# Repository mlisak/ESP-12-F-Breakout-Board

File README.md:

## ESP-12-F Breakout Board
This is a simple plug&play breakout board for ESP-12-F cheap Wi-Fi board (22 pins with SPI, 4 MB flash). The design is small, two-sided, and fits nicely on a breadboard. All 22 pins are available on pin headers. The board includes micro USB port, 3.3 V stabilizer, flash/reset buttons and USB-to-serial converter (CH340G/CH340T). Works well with NodeMCU firmware.

Schematic is based on [this design](https://github.com/markbeee/ESP8266_Breakout_Board).

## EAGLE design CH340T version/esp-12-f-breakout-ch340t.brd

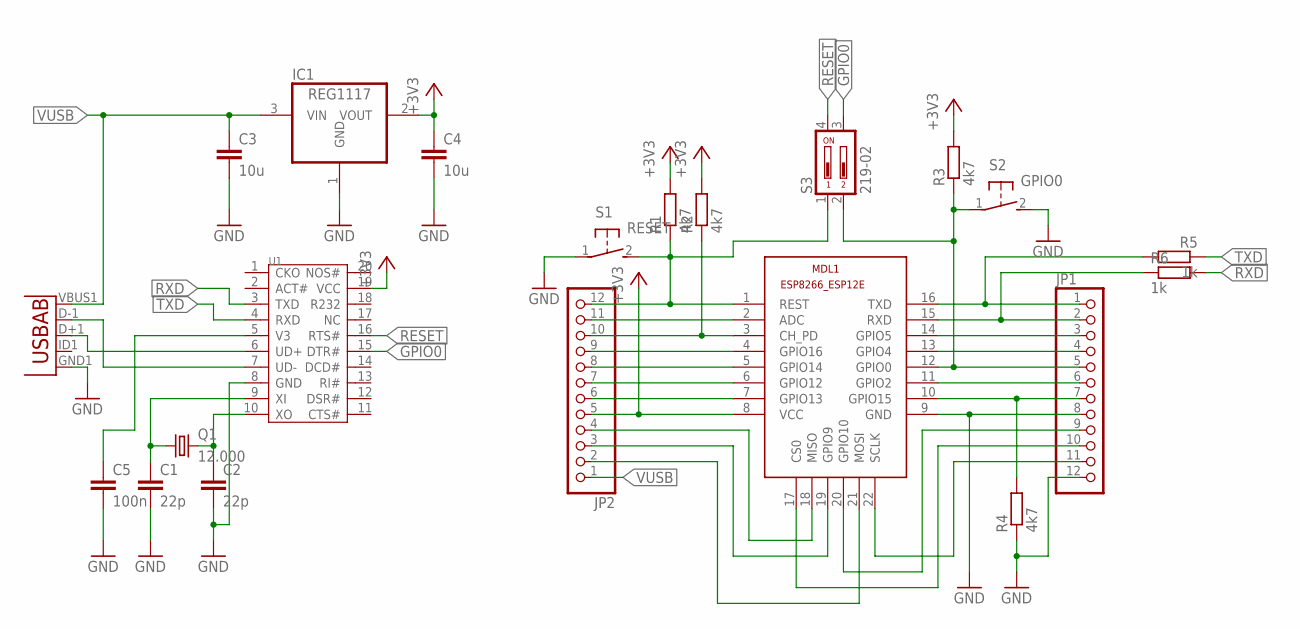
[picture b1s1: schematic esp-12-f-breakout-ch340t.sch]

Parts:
C1, C2: 22p; C0805
C3, C4: 10u; C0805
C5: 100n; C0805
IC1: REG1117; SOT223
JP1, JP2: PINHD-1X12; 1X12
MDL1: ESP8266-12EESP8266-ESP12E; ESP8266-ESP12E
Q1: 12.000; HC49UP
R1, R2, R3, R4: 4k7; M0805
R5, R6: 1k; M0805
S1: RESET; DTSM-3
S2: GPIO0; DTSM-3
S3: 219-02; CTS-219-02
U1: CH340T; SSOP20
U2: USB""; USB-MICRO-SMD

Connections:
+3V3: C4.1, IC1.2 (VOUT), JP2.5, MDL1.8 (VCC), R1.2, R2.2, R3.2, U1.19 (VCC)
GND: C1.2, C2.2, C3.2, C4.2, C5.2, IC1.1 (GND), JP1.8, JP1.12, MDL1.9 (GND), R4.1, S1.1, S2.2, U1.8 (GND), U2.GND1 (GND)
GPIO0: S3.3, U1.15 (DTR#)
unnamed: JP2.12, MDL1.1 (REST), R1.1, S1.2, S3.1
unnamed: JP2.11, MDL1.2 (ADC)
unnamed: JP2.10, MDL1.3 (CH_PD), R2.1
unnamed: JP2.9, MDL1.4 (GPIO16)
unnamed: JP2.8, MDL1.5 (GPIO14)
unnamed: JP2.7, MDL1.6 (GPIO12)
unnamed: JP2.6, MDL1.7 (GPIO13)
unnamed: JP2.4, MDL1.18 (MISO)
unnamed: JP2.3, MDL1.19 (GPIO9)
unnamed: JP1.9, MDL1.20 (GPIO10)
unnamed: JP1.10, MDL1.17 (CS0)
unnamed: JP1.11, MDL1.22 (SCLK)
unnamed: JP2.2, MDL1.21 (MOSI)
unnamed: JP1.7, MDL1.10 (GPIO15), R4.2
unnamed: JP1.6, MDL1.11 (GPIO2)
unnamed: JP1.5, MDL1.12 (GPIO0), R3.1, S2.1, S3.2
unnamed: JP1.4, MDL1.13 (GPIO4)
unnamed: JP1.3, MDL1.14 (GPIO5)
unnamed: JP1.2, MDL1.15 (RXD), R6.1
unnamed: JP1.1, MDL1.16 (TXD), R5.2
unnamed: C1.1, Q1.1, U1.9 (XI)
unnamed: C2.1, Q1.2, U1.10 (XO)
unnamed: U1.7 (UD-), U2.D-1 (D-)
unnamed: U1.6 (UD+), U2.D+1 (D+)
RESET: S3.4, U1.16 (RTS#)
RXD: R6.2, U1.3 (TXD)
TXD: R5.1, U1.4 (RXD)
V3: C5.1, U1.5 (V3)
VUSB: C3.1, IC1.3 (VIN), JP2.1, U2.VBUS1 (VBUS)

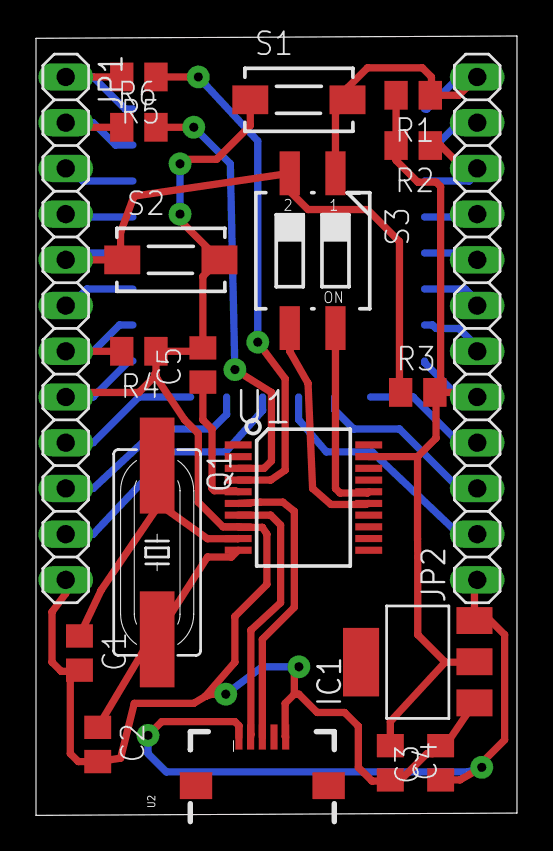
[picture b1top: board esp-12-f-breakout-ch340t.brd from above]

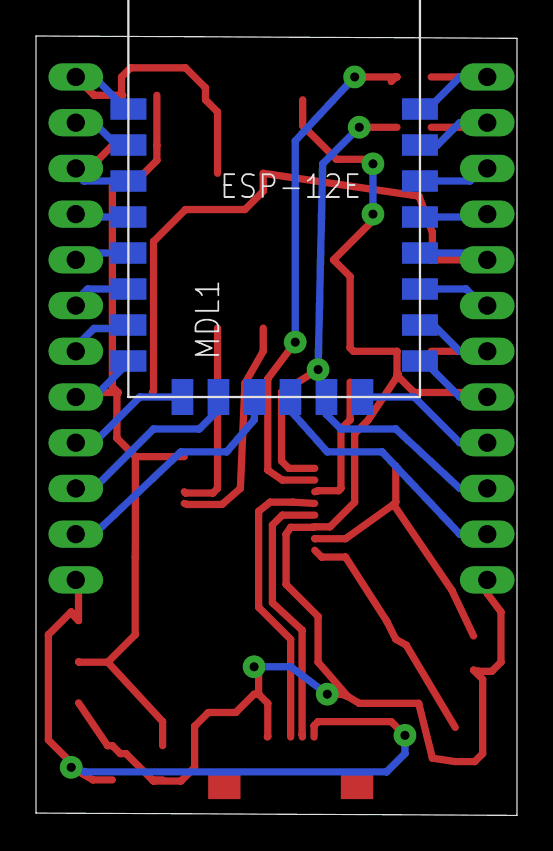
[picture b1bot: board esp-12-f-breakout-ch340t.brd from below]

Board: 2 copper layers, 26.7 x 43.3 mm, 22 parts (2 on the bottom side), 32 nets.

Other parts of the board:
U$1: MITSUDOMOE

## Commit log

2016-05-03 USB +5V pin added to pin headers
    - Additional GND pin added
    - Stabilizer layout rearranged
    - Vias diameter slightly increased
    - Drill-aid (0.4 mm) added
